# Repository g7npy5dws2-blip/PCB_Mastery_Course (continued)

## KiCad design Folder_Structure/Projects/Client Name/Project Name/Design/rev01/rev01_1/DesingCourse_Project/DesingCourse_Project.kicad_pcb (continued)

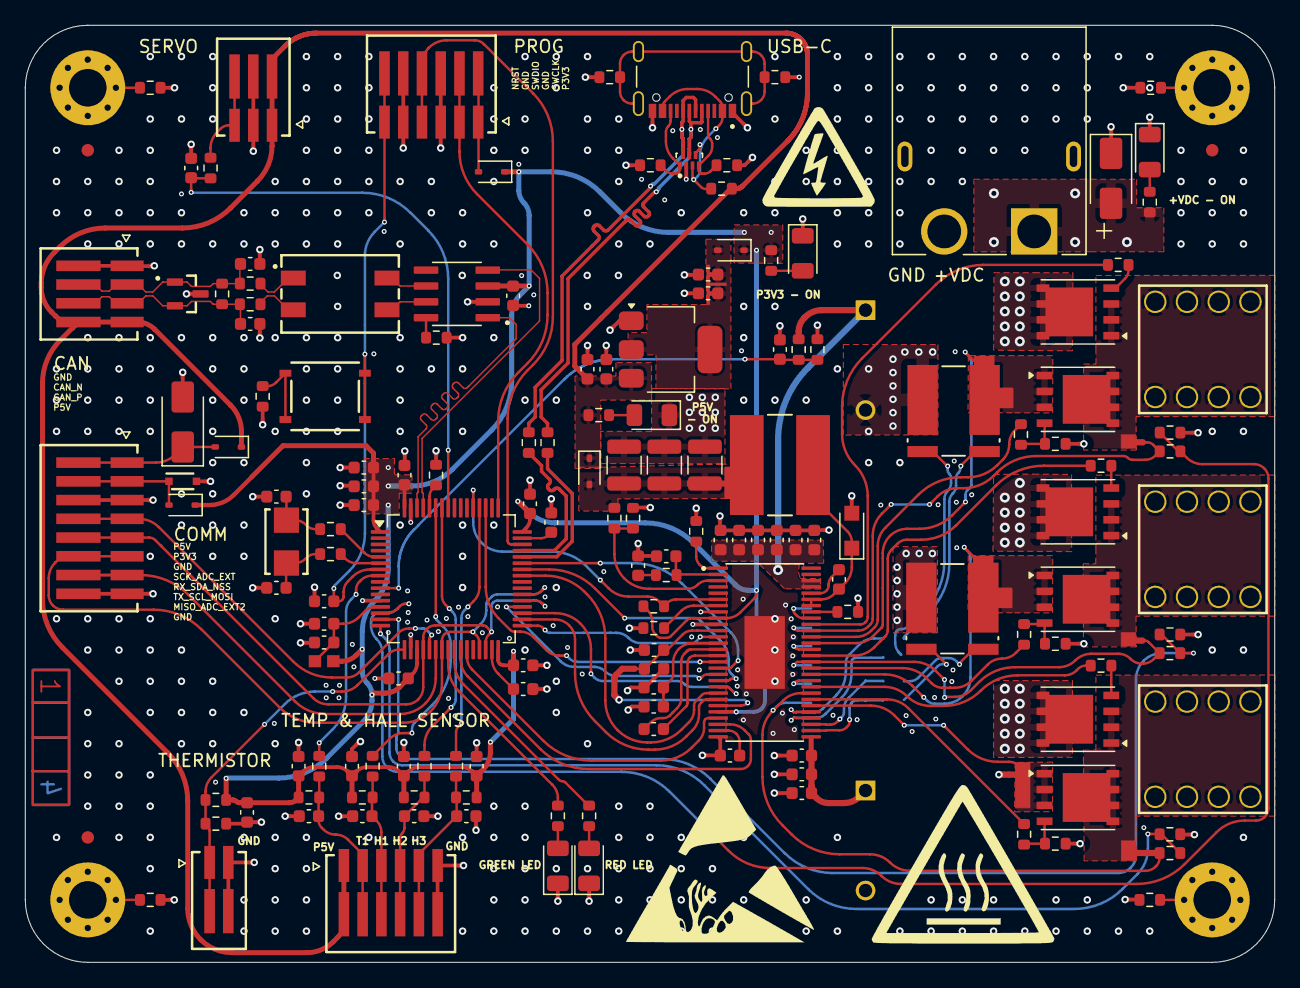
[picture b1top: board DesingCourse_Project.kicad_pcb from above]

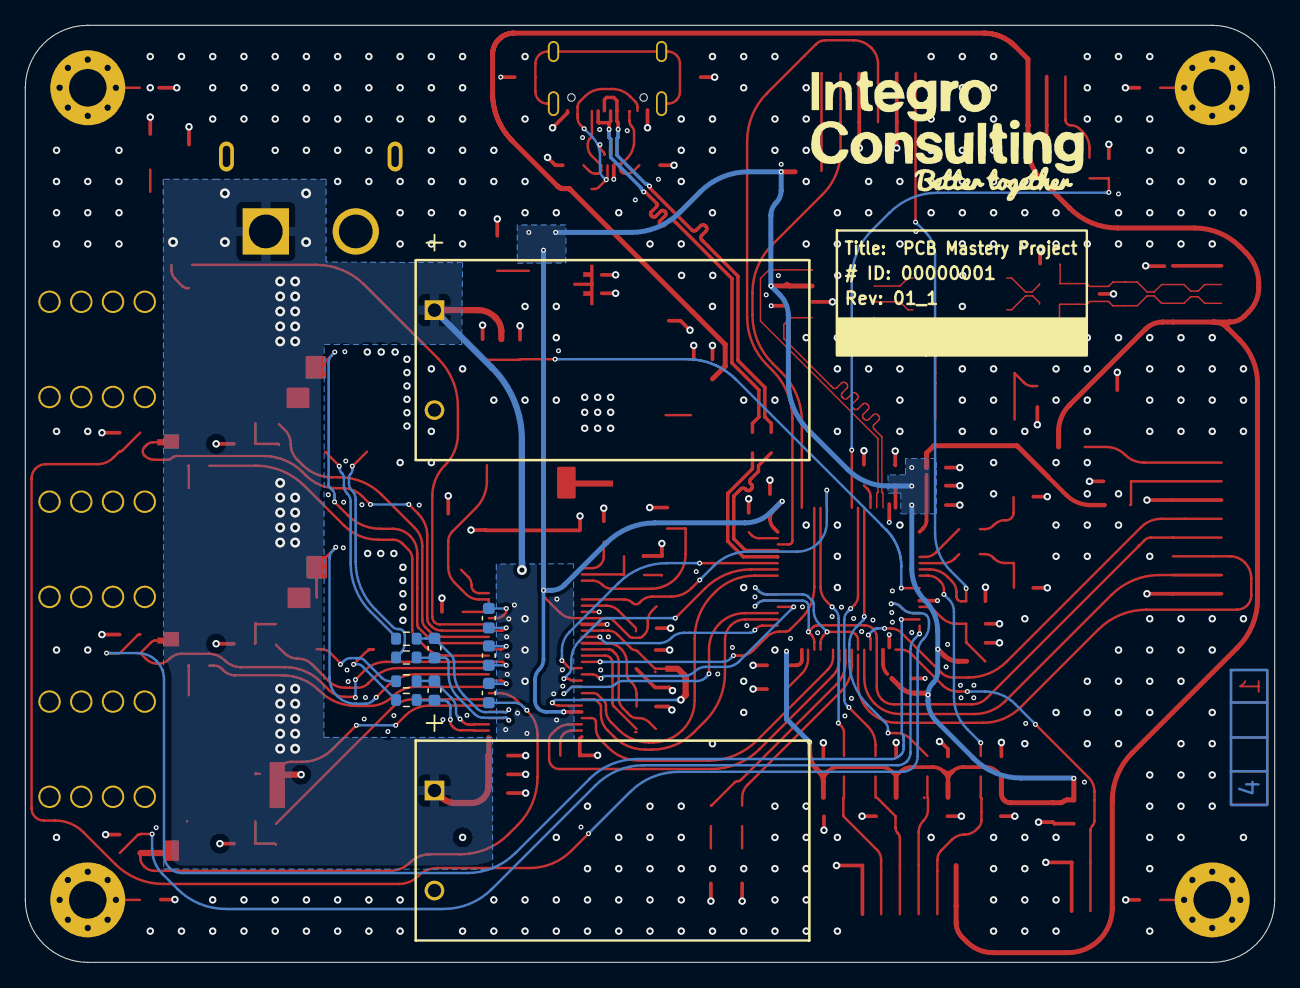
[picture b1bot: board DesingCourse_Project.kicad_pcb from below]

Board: 4 copper layers, 100.0 x 75.0 mm, 185 parts (13 on the bottom side), 125 nets.

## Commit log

2026-01-15 Update 1
    - Creat SCH & PCB template
2026-01-19 Update 2
    KiCAD project creation
    Schematica flat hierarqchy with block diagram
2026-01-21 Update 3
    MCU SCH done
2026-01-22 Update 4
    Finish the MOSFET DRIVE page
2026-01-23 Update 5
    small updates and 3D body created for the 22uH inductor
2026-01-27 Update 6
    SCH and LIB for MOSFET page done, missing passive components
2026-01-27 Update 7
    Update on 3D of coil
2026-01-28 Update 8
    Page 1 finished, INPUT finished, Start of USB-C
2026-01-29 Update 9
    USC-C & STEP_DOWN are DONE // MCU missing TVS diodes on P3V3 & P5V
2026-01-30 Update 10
    All done up to MOSFET page, replace all connected to actual PN
2026-02-03 Update 11
    SCH finishe, missing the labels and logos and adding all passive components
2026-02-04 Update 12
    Until STEP-DOWN page, all components have complete libraries.
    Creation and incluison of all logos and labels libraries
2026-02-05 Update13
    Still working on FP for the MCU
2026-02-06 Update14
    All components with FP, missing the block diagram
2026-02-06 Update 15
    Ready for DRC
2026-02-09 Update 16
    Initial component placement done
2026-02-10 Update17
    Design rules and stack defined.
    Check againg DR and proceed with layout.
2026-02-16 Update18
    Layout finished, clean up or layout and designators.
2026-02-17 Update19
    PCB finished before applying curved traces
2026-02-18 Update20
    DRC "clear".
    Create gerber files
2026-02-19 Update21
    Save before created manuf and assy files
2026-02-19 Update22
    Project finished.
    Ready for manuf
